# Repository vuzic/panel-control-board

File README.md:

# Panel Control Hardware

## Power

### Requirements 
* Power button which either boots or sends a signal to the RPI to shutdown.
* Battery status indication (can be crude, maybe just color or flashing to indicate low battery vs charging vs charged)
* Should not draw too much current when off but fully charged
* OE needs to be disabled on panels when PI is off
* MCU with analog voltage from battery
* MCU needs to tell RPI to shut down when battery is <10%

### Ideas
* Use MOSFET rated for 15W (5V/3A) to power on the RPI
* RPI GPIO to act as a power status pin. Shutdown sequence waits for a level change on this pin before cutting the power.
    * High means PI is shutting down; when it goes low, its finished powering off.
# LED Interface

(old README, needs update)

This is a hat designed for a Raspberry Pi Zero. It consists of two headers for I2S microphones (the sort of which are availble for under 2$ on aliexpress) and two level shifted outputs.

The primary purpose is to control 4-wire LED strips using the four pin header. This should also be able to provide the Pi Zero with power.

There's also a HUB-75 connector for driving LED panels. This might be less useful, and probably wasn't neccessary. (These are much better suited to be driven off a PI 3 or 4 if the
frame rate or color depth matters, and some research into [hzeller's](https://github.com/hzeller/rpi-rgb-led-matrix) excellent library points out that the I2S CLK pin is also the same
as the PWM pin which drives the OE signal to the panels for better performance. I'm using a different pin mapping anyway (TODO: write it down..) so it wont work out of the box in any case.)

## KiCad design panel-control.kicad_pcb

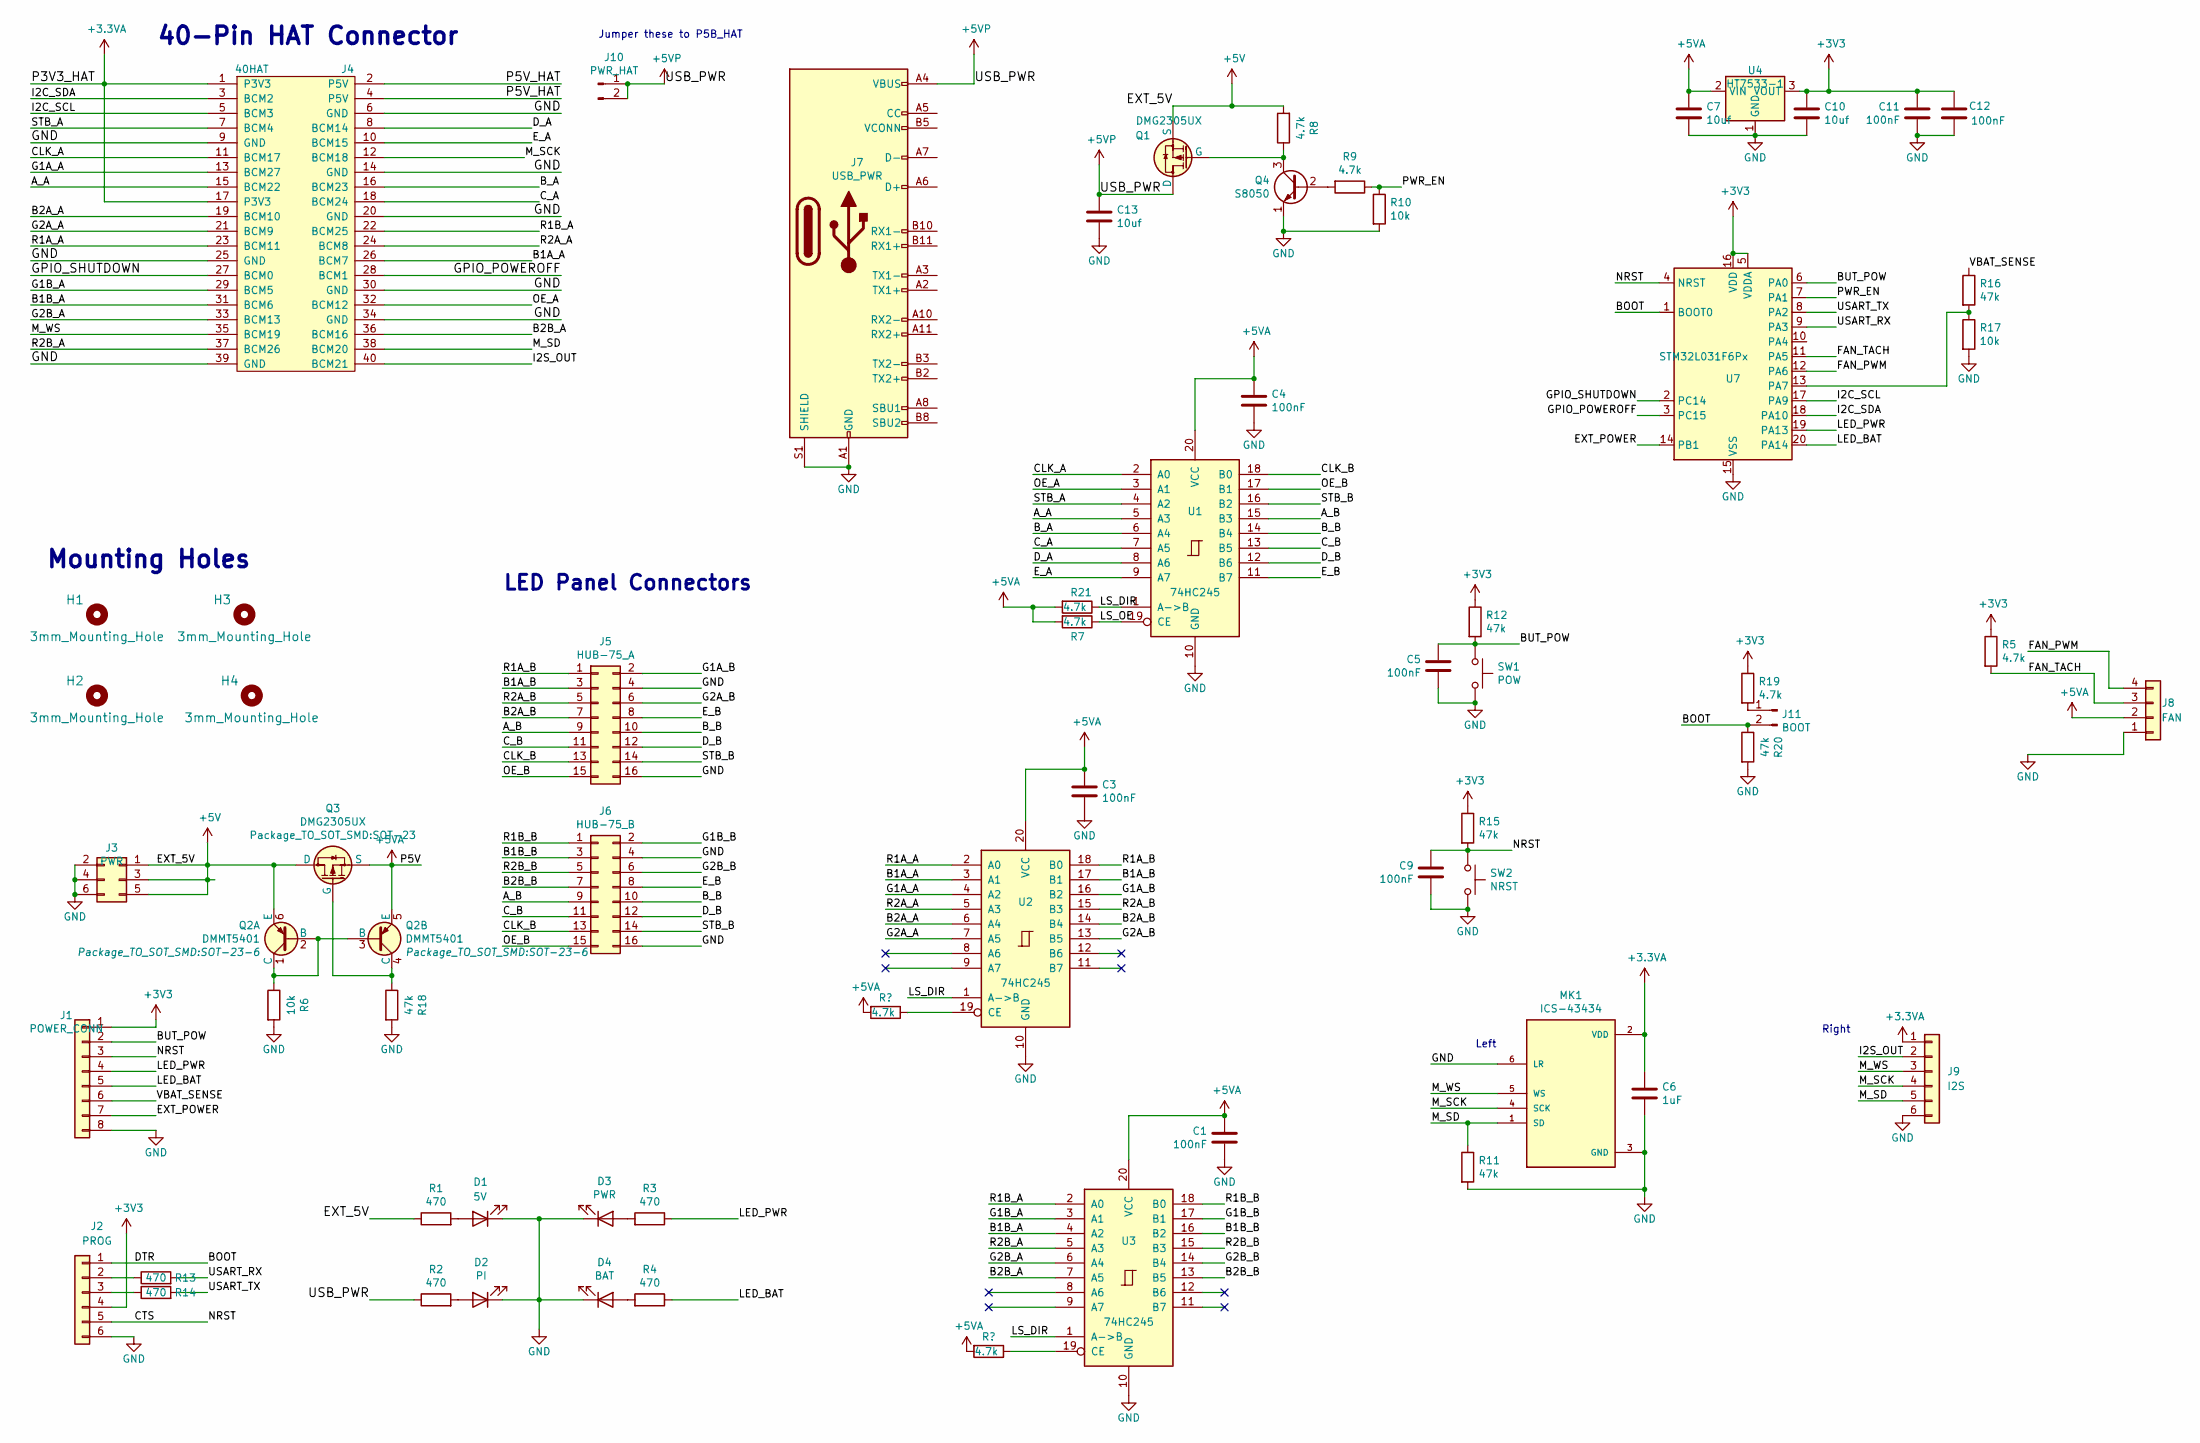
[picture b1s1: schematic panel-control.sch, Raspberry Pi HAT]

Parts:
C1, C3, C4, C5, C9, C11, C12: 100nF; C_0603_1608Metric; LCSC C14663
C6: 1uF; C_0603_1608Metric; LCSC C15849
C7, C10, C13: 10uf; C_0603_1608Metric; LCSC C19702
D1: 5V; LED_0603_1608Metric; LCSC C72038
D2: PI; LED_0603_1608Metric; LCSC C72038
D3: PWR; LED_0805_2012Metric; LCSC C2293
D4: BAT; LED_0805_2012Metric; LCSC C84256
H1, H2, H3, H4: 3mm_Mounting_Hole; NPTH_3mm_ID
J1: POWER_CONN; Molex_200528-0080_1x08-1MP_P1.00mm_Horizontal
J2: PROG; PinHeader_1x06_P2.54mm_Vertical
J3: PWR; PinHeader_2x03_P2.54mm_Vertical
J4: 40HAT; PinSocket_2x20_P2.54mm_Vertical
J5: HUB-75_A; IDC-Header_2x08_P2.54mm_Vertical
J6: HUB-75_B; IDC-Header_2x08_P2.54mm_Vertical
J7: USB_PWR; USB_C_Receptacle_GCT_USB4085
J8: FAN; FanPinHeader_1x04_P2.54mm_Vertical
J9: I2S; Molex_200528-0060_1x06-1MP_P1.00mm_Horizontal
J10: PWR_HAT; PinHeader_1x02_P2.54mm_Vertical
J11: BOOT; PinHeader_1x02_P2.54mm_Vertical
MK1: ICS-43434; I2S-MIC_DIP-6
Q1, Q3: DMG2305UX; SOT-23; LCSC C144153
Q2: DMMT5401; SOT-23-6; LCSC C154733
Q4: S8050; SOT-23; LCSC C2146
R1, R2, R3, R4, R13, R14: 470; R_0402_1005Metric; LCSC C25117
R5, R7, R8, R9, R19, R21: 4.7k; R_0402_1005Metric; LCSC C25900
R6: 10k; R_0402_1005Metric
R10, R17: 10k; R_0402_1005Metric; LCSC C25744
R11, R16: 47k; R_0402_1005Metric; LCSC C25792
R12, R15: 47k; R_0402_1005Metric; LCSC C25900
R18, R20: 47k; R_0402_1005Metric
SW1: POW; SW_Push_1P1T_NO_6x6mm_H9.5mm
SW2: NRST; SW_Push_1P1T_NO_6x6mm_H9.5mm
U1, U2, U3: 74HC245; SSOP-20_4.4x6.5mm_P0.65mm; LCSC C6779
U4: HT7533-1; SOT-89-3; LCSC C14289
U7: STM32L031F6Px; TSSOP-20_4.4x6.5mm_P0.65mm; LCSC C115208

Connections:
+3.3VA: C6.1, J4.1 (P3V3), J4.17 (P3V3), J9.1, MK1.2 (VDD)
+3V3: C10.1, C11.2, C12.2, J1.1, J2.4, R5.1, R12.1, R15.1, R19.1, U4.3 (VOUT), U7.5 (VDDA), U7.16 (VDD)
+5V: J3.1, J3.3, J3.5, Q1.2 (S), Q2.6 (E), Q3.3 (D), R1.1, R8.2
+5VA: C1.1, C3.1, C4.1, C7.1, J8.2, Q2.5 (E), Q3.2 (S), R7.2, R21.2, U1.20 (VCC), U2.20 (VCC), U3.20 (VCC), U4.2 (VIN); also elsewhere on the board
+5VP: C13.1, J7.A4 (VBUS), J7.A9 (VBUS), J7.B4 (VBUS), J7.B9 (VBUS), J10.1, J10.2, Q1.3 (D), R2.1
/A_A: J4.15 (BCM22), U1.5 (A3)
/A_B: J5.9, J6.9, U1.15 (B3)
/B1A_A: J4.26 (BCM7), U2.3 (A1)
/B1A_B: J5.3, U2.17 (B1)
/B1B_A: J4.31 (BCM6), U3.4 (A2)
/B1B_B: J6.3, U3.16 (B2)
/B2A_A: J4.19 (BCM10), U2.6 (A4)
/B2A_B: J5.7, U2.14 (B4)
/B2B_A: J4.36 (BCM16), U3.7 (A5)
/B2B_B: J6.7, U3.13 (B5)
/BOOT: J2.1, J11.2, R20.1, U7.1 (BOOT0)
/BUT_POW: C5.2, J1.2, R12.2, SW1.1, U7.6 (PA0)
/B_A: J4.16 (BCM23), U1.6 (A4)
/B_B: J5.10, J6.10, U1.14 (B4)
/CLK_A: J4.11 (BCM17), U1.2 (A0)
/CLK_B: J5.13, J6.13, U1.18 (B0)
/CTS: C9.2, J1.3, J2.5, R15.2, SW2.1, U7.4 (NRST)
/C_A: J4.18 (BCM24), U1.7 (A5)
/C_B: J5.11, J6.11, U1.13 (B5)
/D_A: J4.8 (BCM14), U1.8 (A6)
/D_B: J5.12, J6.12, U1.12 (B6)
/EXT_POWER: J1.7, U7.14 (PB1)
/E_A: J4.10 (BCM15), U1.9 (A7)
/E_B: J5.8, J6.8, U1.11 (B7)
/FAN_PWM: J8.4, U7.12 (PA6)
/FAN_TACH: J8.3, R5.2, U7.11 (PA5)
/G1A_A: J4.13 (BCM27), U2.4 (A2)
/G1A_B: J5.2, U2.16 (B2)
/G1B_A: J4.29 (BCM5), U3.3 (A1)
/G1B_B: J6.2, U3.17 (B1)
/G2A_A: J4.21 (BCM9), U2.7 (A5)
/G2A_B: J5.6, U2.13 (B5)
/G2B_A: J4.33 (BCM13), U3.6 (A4)
/G2B_B: J6.6, U3.14 (B4)
/GPIO_POWEROFF: J4.28 (BCM1), U7.3 (PC15)
/GPIO_SHUTDOWN: J4.27 (BCM0), U7.2 (PC14)
/I2C_SCL: J4.5 (BCM3), U7.17 (PA9)
/I2C_SDA: J4.3 (BCM2), U7.18 (PA10)
/I2S_OUT: J4.40 (BCM21), J9.2
/LED_BAT: J1.5, R4.1, U7.20 (PA14)
/LED_PWR: J1.4, R3.1, U7.19 (PA13)
/LS_DIR: R21.1, U1.1 (A->B), U2.1 (A->B), U3.1 (A->B)
/LS_OE: R7.1, U1.19 (CE)
/M_SCK: J4.12 (BCM18), J9.4, MK1.4 (SCK)
/M_SD: J4.38 (BCM20), J9.5, MK1.1 (SD), R11.1
/M_WS: J4.35 (BCM19), J9.3, MK1.5 (WS)
/OE_A: J4.32 (BCM12), U1.3 (A1)
/OE_B: J5.15, J6.15, U1.17 (B1)
/P5V_HAT: J4.2 (P5V), J4.4 (P5V)
/PWR_EN: R9.1, R10.1, U7.7 (PA1)
/R1A_A: J4.23 (BCM11), U2.2 (A0)
/R1A_B: J5.1, U2.18 (B0)
/R1B_A: J4.22 (BCM25), U3.2 (A0)
/R1B_B: J6.1, U3.18 (B0)
/R2A_A: J4.24 (BCM8), U2.5 (A3)
/R2A_B: J5.5, U2.15 (B3)
/R2B_A: J4.37 (BCM26), U3.5 (A3)
/R2B_B: J6.5, U3.15 (B3)
/STB_A: J4.7 (BCM4), U1.4 (A2)
/STB_B: J5.14, J6.14, U1.16 (B2)
/USART_RX: R13.2, U7.9 (PA3)
/USART_TX: R14.2, U7.8 (PA2)
/VBAT_SENSE: J1.6, R16.1
GND: C1.2, C3.2, C4.2, C5.1, C6.2, C7.2, C9.1, C10.2, C11.1, C12.1, C13.2, D1.1 (K), D2.1 (K), D3.1 (K), D4.1 (K), J1.8, J2.6, J3.2, J3.4, J3.6, J4.6 (GND), J4.9 (GND), J4.14 (GND), J4.20 (GND), J4.25 (GND), J4.30 (GND), J4.34 (GND), J4.39 (GND), J5.4, J5.16, J6.4, J6.16, J7.A1 (GND), J7.A12 (GND), J7.B1 (GND), J7.B12 (GND), J7.S1 (SHIELD), J8.1, J9.6, MK1.3 (GND), MK1.6 (LR), Q4.1 (E), R6.2, R10.2, R11.2, R17.2, R18.2, R20.2, SW1.2, SW2.2, U1.10 (GND), U2.10 (GND), U3.10 (GND), U4.1 (GND), U7.15 (VSS)
unnamed: D1.2 (A), R1.2
unnamed: D2.2 (A), R2.2
unnamed: D3.2 (A), R3.2
unnamed: D4.2 (A), R4.2
unnamed: J2.2, R13.1
unnamed: J2.3, R14.1
unnamed: J11.1, R19.2
unnamed: Q1.1 (G), Q4.3 (C), R8.1
unnamed: Q2.1 (C), Q2.2 (B), Q2.3 (B), R6.1
unnamed: Q2.4 (C), Q3.1 (G), R18.1
unnamed: Q4.2 (B), R9.2
unnamed: R16.2, R17.1, U7.13 (PA7)
unnamed 87: U2.19 (CE); also elsewhere on the board
unnamed 88: U3.19 (CE); also elsewhere on the board

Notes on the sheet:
Mounting Holes
40-Pin HAT Connector
LED Panel Connectors
Left
Right
Jumper these to P5B_HAT

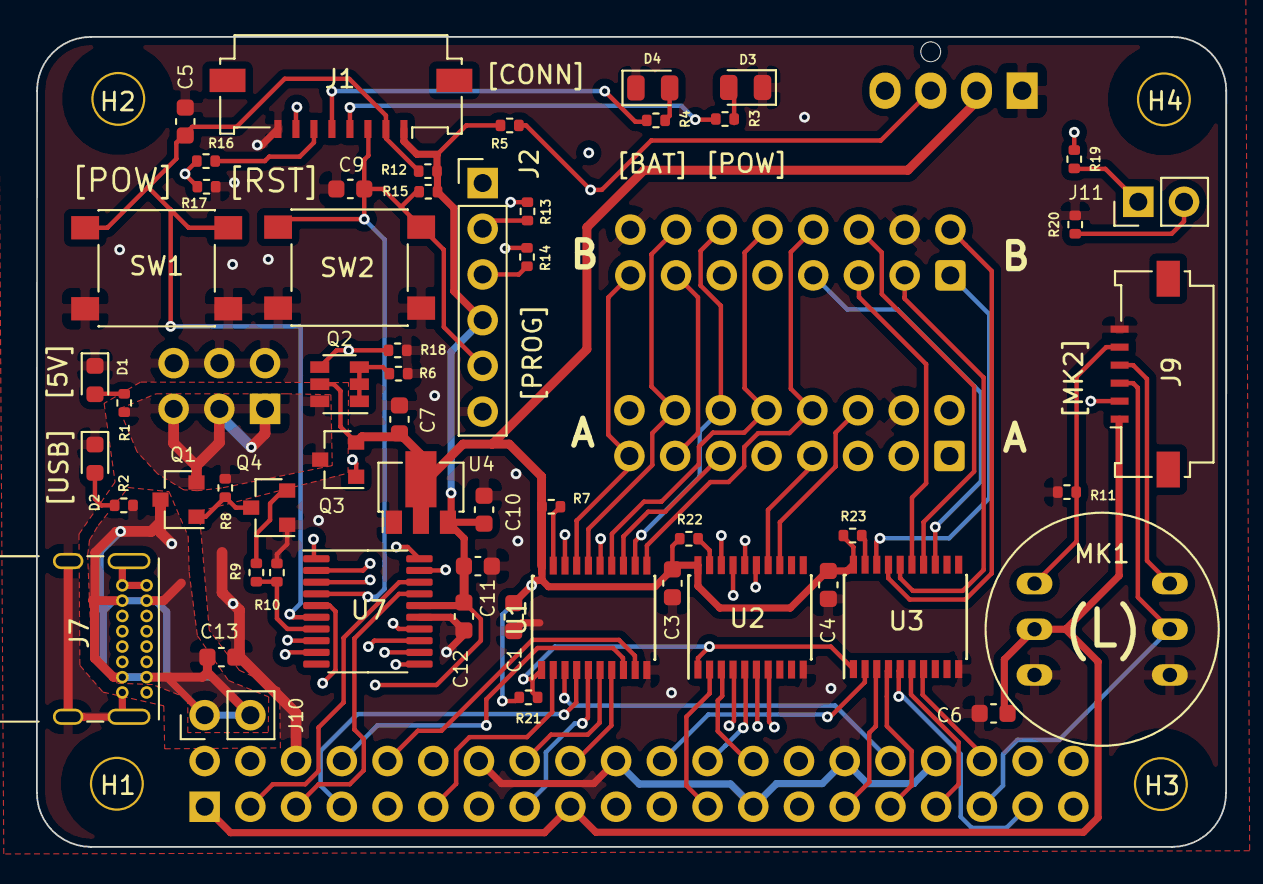
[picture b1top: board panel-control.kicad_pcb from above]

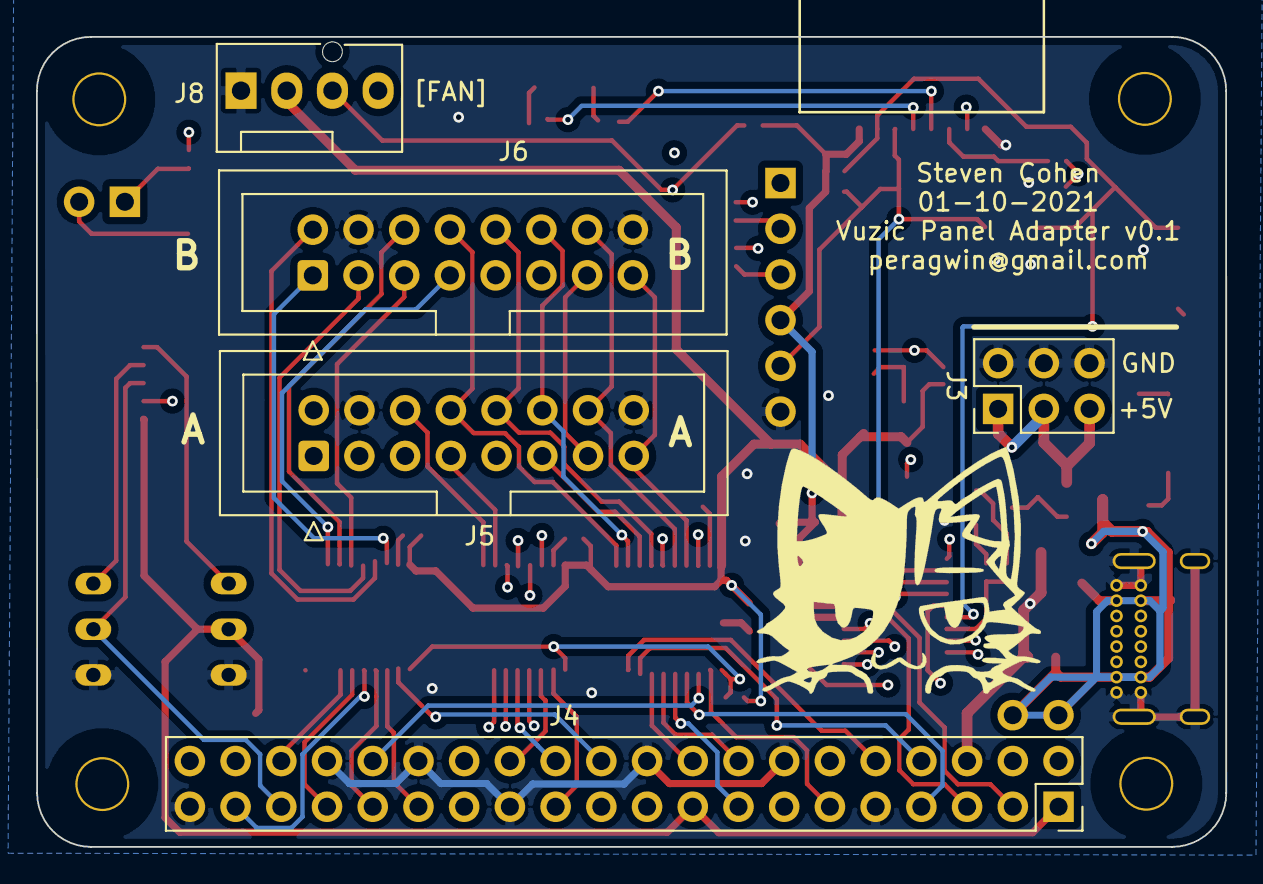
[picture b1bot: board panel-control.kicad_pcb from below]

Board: 4 copper layers, 66.1 x 45.0 mm, 65 parts (5 on the bottom side), 83 nets.

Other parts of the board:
R22, R23: 4.7k; R_0402_1005Metric

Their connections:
+5VA: R22.2, R23.2; also elsewhere on the board
unnamed 87: R22.1; also elsewhere on the board
unnamed 88: R23.1; also elsewhere on the board

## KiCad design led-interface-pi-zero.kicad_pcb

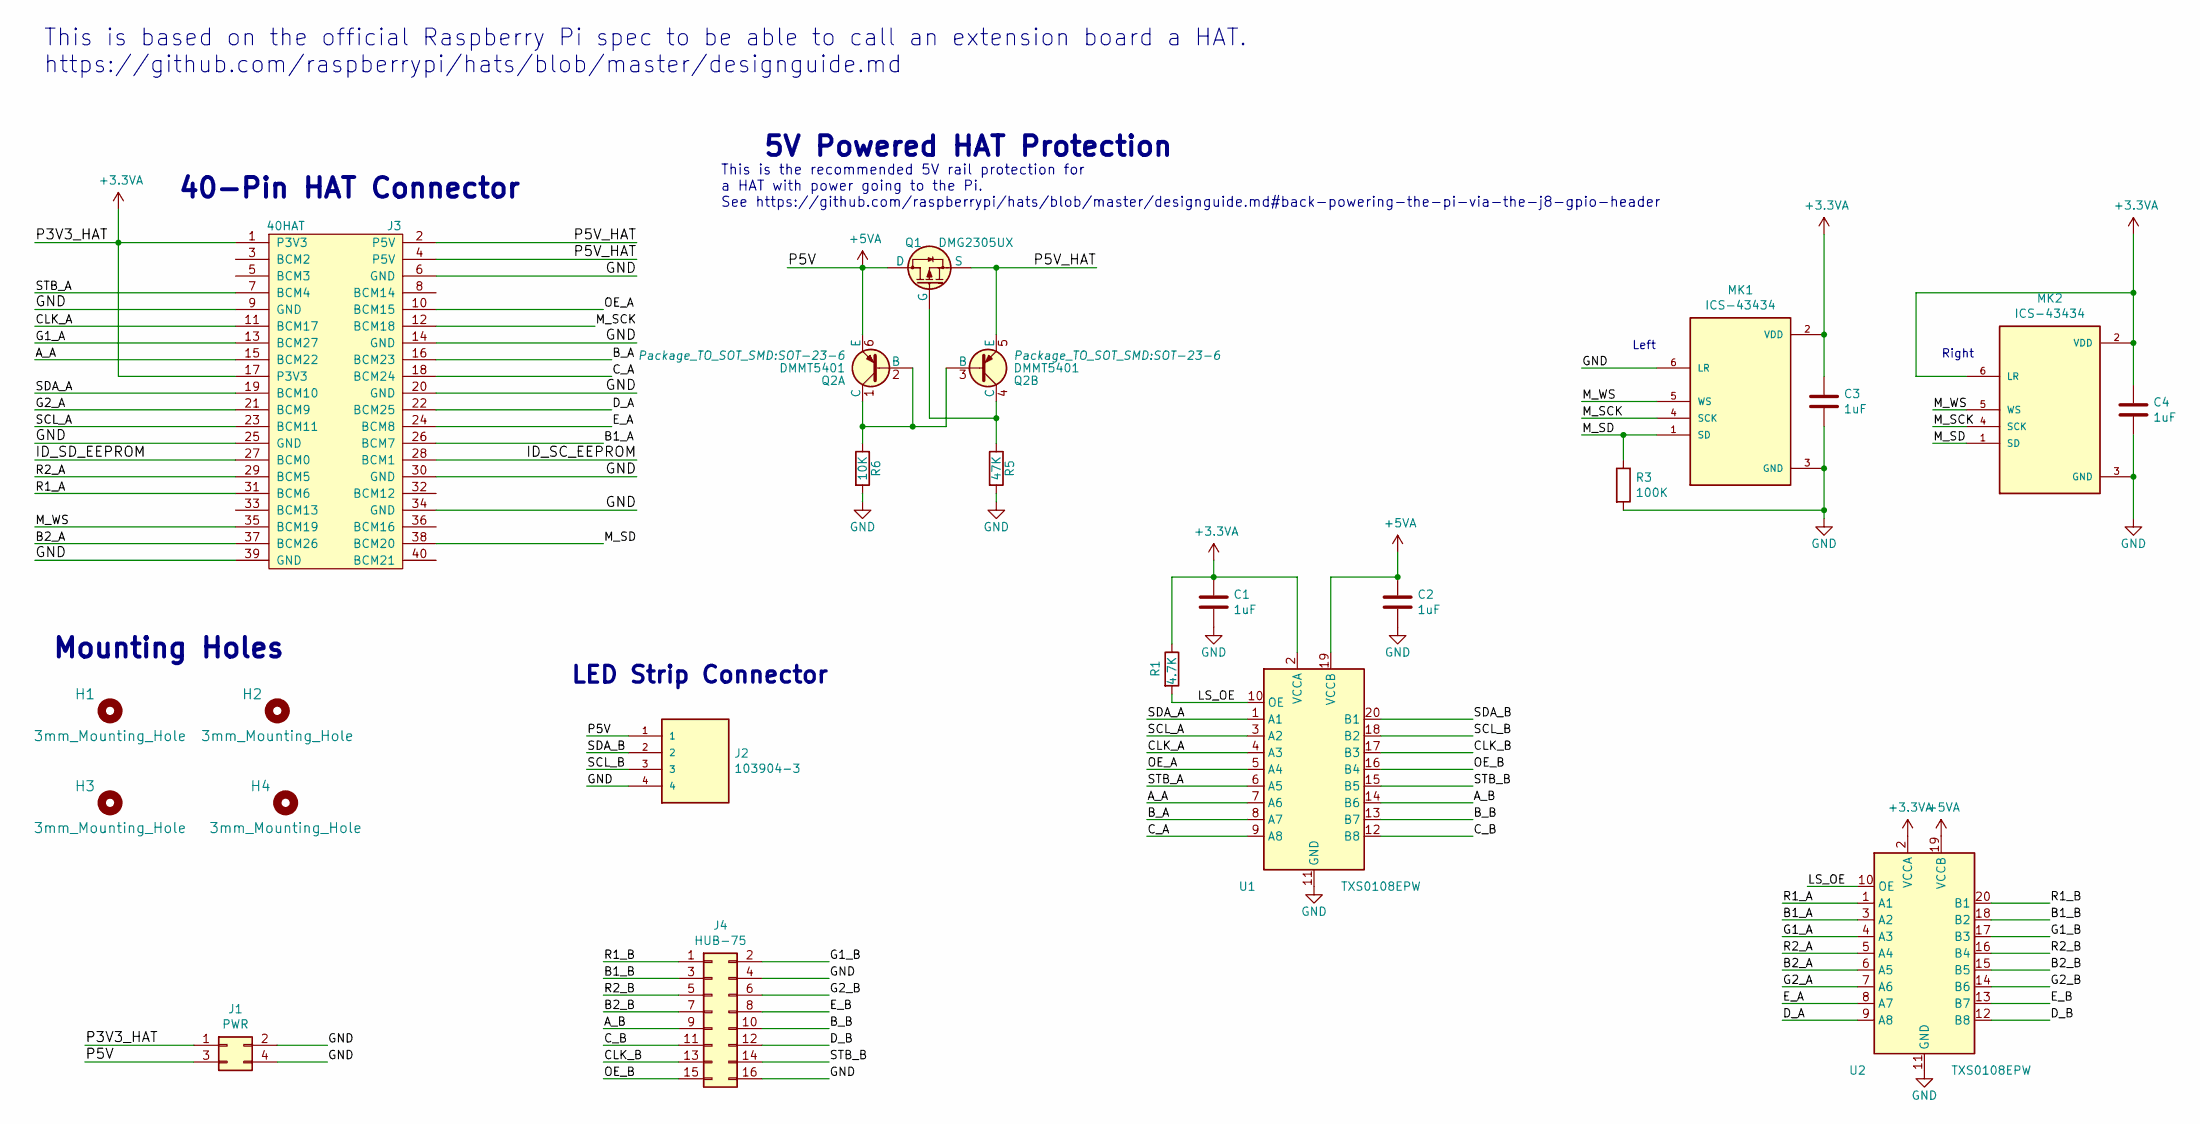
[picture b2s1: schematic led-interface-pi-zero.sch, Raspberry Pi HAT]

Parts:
C1, C2, C3, C4: 1uF; C_0603_1608Metric_Pad1.08x0.95mm_HandSolder
H1, H2, H3, H4: 3mm_Mounting_Hole; NPTH_3mm_ID
J1: PWR; PinHeader_2x02_P2.54mm_Vertical
J2: 103904-3; TE_103904-3
J3: 40HAT; PinSocket_2x20_P2.54mm_Vertical
J4: HUB-75; TE_5-103167-5
MK1, MK2: ICS-43434; I2S-MIC_DIP-6
Q1: DMG2305UX; SOT-23
Q2: DMMT5401; SOT-23-6
R1: 4.7K; C_0603_1608Metric_Pad1.08x0.95mm_HandSolder
R3: 100K; R_0603_1608Metric_Pad0.98x0.95mm_HandSolder
R5: 47K; R_0603_1608Metric_Pad0.84x1.00mm_HandSolder
R6: 10K; R_0603_1608Metric_Pad0.84x1.00mm_HandSolder
U1, U2: TXS0108EPW; TSSOP-20_4.4x6.5mm_P0.65mm

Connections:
+3.3VA: C1.1, C3.1, C4.1, J1.1, J3.1 (P3V3), J3.17 (P3V3), MK1.2 (VDD), MK2.2 (VDD), MK2.6 (LR), R1.1, U1.2 (VCCA), U2.2 (VCCA)
+5VA: C2.1, J1.3, J2.1, Q1.3 (D), Q2.6 (E), U1.19 (VCCB), U2.19 (VCCB)
/A_A: J3.15 (BCM22), U1.7 (A6)
/A_B: J4.9, U1.14 (B6)
/B1_A: J3.26 (BCM7), U2.3 (A2)
/B1_B: J4.3, U2.18 (B2)
/B2_A: J3.37 (BCM26), U2.6 (A5)
/B2_B: J4.7, U2.15 (B5)
/B_A: J3.16 (BCM23), U1.8 (A7)
/B_B: J4.10, U1.13 (B7)
/CLK_A: J3.11 (BCM17), U1.4 (A3)
/CLK_B: J4.13, U1.17 (B3)
/C_A: J3.18 (BCM24), U1.9 (A8)
/C_B: J4.11, U1.12 (B8)
/D_A: J3.22 (BCM25), U2.9 (A8)
/D_B: J4.12, U2.12 (B8)
/E_A: J3.24 (BCM8), U2.8 (A7)
/E_B: J4.8, U2.13 (B7)
/G1_A: J3.13 (BCM27), U2.4 (A3)
/G1_B: J4.2, U2.17 (B3)
/G2_A: J3.21 (BCM9), U2.7 (A6)
/G2_B: J4.6, U2.14 (B6)
/ID_SC_EEPROM: J3.28 (BCM1)
/ID_SD_EEPROM: J3.27 (BCM0)
/LS_OE: R1.2, U1.10 (OE), U2.10 (OE)
/M_SCK: J3.12 (BCM18), MK1.4 (SCK), MK2.4 (SCK)
/M_SD: J3.38 (BCM20), MK1.1 (SD), MK2.1 (SD), R3.1
/M_WS: J3.35 (BCM19), MK1.5 (WS), MK2.5 (WS)
/OE_A: J3.10 (BCM15), U1.5 (A4)
/OE_B: J4.15, U1.16 (B4)
/P5V_HAT: J3.2 (P5V), J3.4 (P5V), Q1.2 (S), Q2.5 (E)
/R1_A: J3.31 (BCM6), U2.1 (A1)
/R1_B: J4.1, U2.20 (B1)
/R2_A: J3.29 (BCM5), U2.5 (A4)
/R2_B: J4.5, U2.16 (B4)
/SCL_A: J3.23 (BCM11), U1.3 (A2)
/SCL_B: J2.3, U1.18 (B2)
/SDA_A: J3.19 (BCM10), U1.1 (A1)
/SDA_B: J2.2, U1.20 (B1)
/STB_A: J3.7 (BCM4), U1.6 (A5)
/STB_B: J4.14, U1.15 (B5)
GND: C1.2, C2.2, C3.2, C4.2, J1.2, J1.4, J2.4, J3.6 (GND), J3.9 (GND), J3.14 (GND), J3.20 (GND), J3.25 (GND), J3.30 (GND), J3.34 (GND), J3.39 (GND), J4.4, J4.16, MK1.3 (GND), MK1.6 (LR), MK2.3 (GND), R3.2, R5.2, R6.2, U1.11 (GND), U2.11 (GND)
unnamed: Q1.1 (G), Q2.4 (C), R5.1
unnamed: Q2.1 (C), Q2.2 (B), Q2.3 (B), R6.1

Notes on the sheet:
5V Powered HAT Protection
This is the recommended 5V rail protection for a HAT with power going to the Pi. See https://github.com/raspberrypi/hats/blob/master/designguide.md#back-powering-the-pi-via-the-j8-gpio-header
Mounting Holes
40-Pin HAT Connector
This is based on the official Raspberry Pi spec to be able to call an extension board a HAT. https://github.com/raspberrypi/hats/blob/master/designguide.md
LED Strip Connector
Left
Right

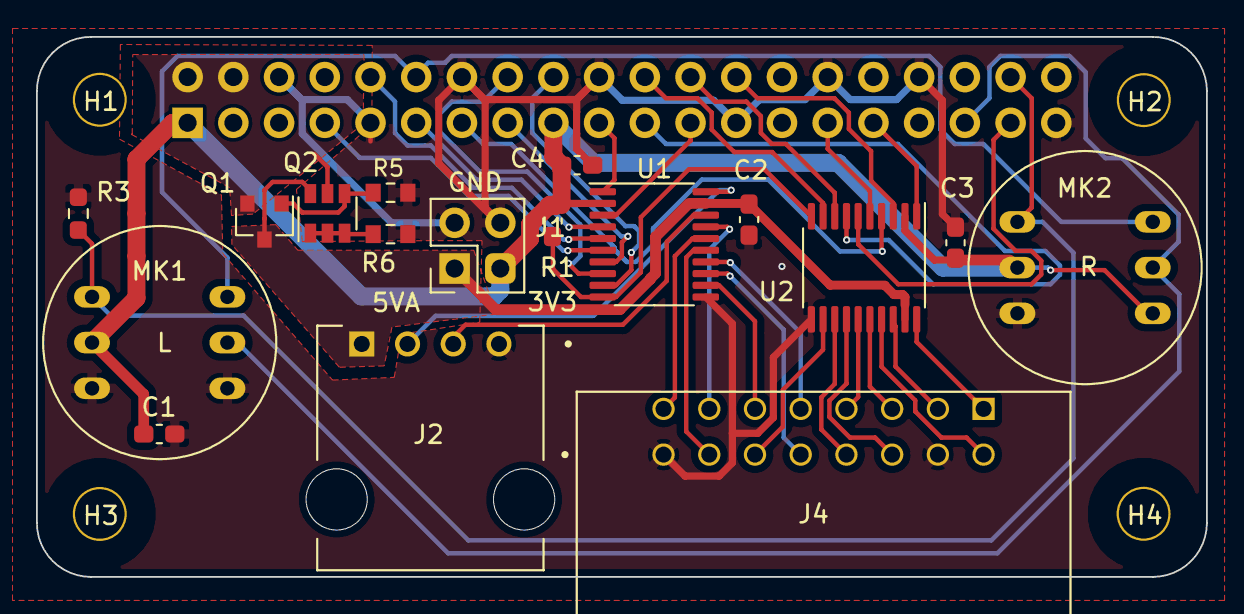
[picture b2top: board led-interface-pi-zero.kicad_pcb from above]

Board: 4 copper layers, 65.0 x 30.0 mm, 22 parts (1 on the bottom side), 42 nets.

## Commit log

2020-11-13 add readme
2020-11-13 add mit license
2021-01-07 work on schematic for panel controller
2021-01-07 fix labels and tweak pwr_en
2021-01-07 mainly finished schematic revision
2021-01-07 update pcb from new sch
2021-01-07 add fan connector to sch
2021-01-08 fix footprints
2021-01-08 add rescue lib
2021-01-08 work on new pcb layout
2021-01-08 start laying traces
2021-01-08 sort of finished layout
2021-01-08 nearly ready to submit
2021-01-10 tweaks to components
2021-01-10 maybe finished revision with micro usb output
2021-01-11 better reverse current protection and usb-c power
2021-01-11 more revisions, maybe ready to submit
2021-01-12 tweak
2021-01-12 finally submitted
2021-01-13 annotate sch
